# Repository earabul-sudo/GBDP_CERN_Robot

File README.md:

# GBDP_CERN_Robot

The report "20200524_PMReport_EA_04.pdf" can be read as the overview of the project.

The Complete CAD model can be found in;

https://a360.co/3e9NEjW

For any issues, please contact -> ea485@bath.ac.uk

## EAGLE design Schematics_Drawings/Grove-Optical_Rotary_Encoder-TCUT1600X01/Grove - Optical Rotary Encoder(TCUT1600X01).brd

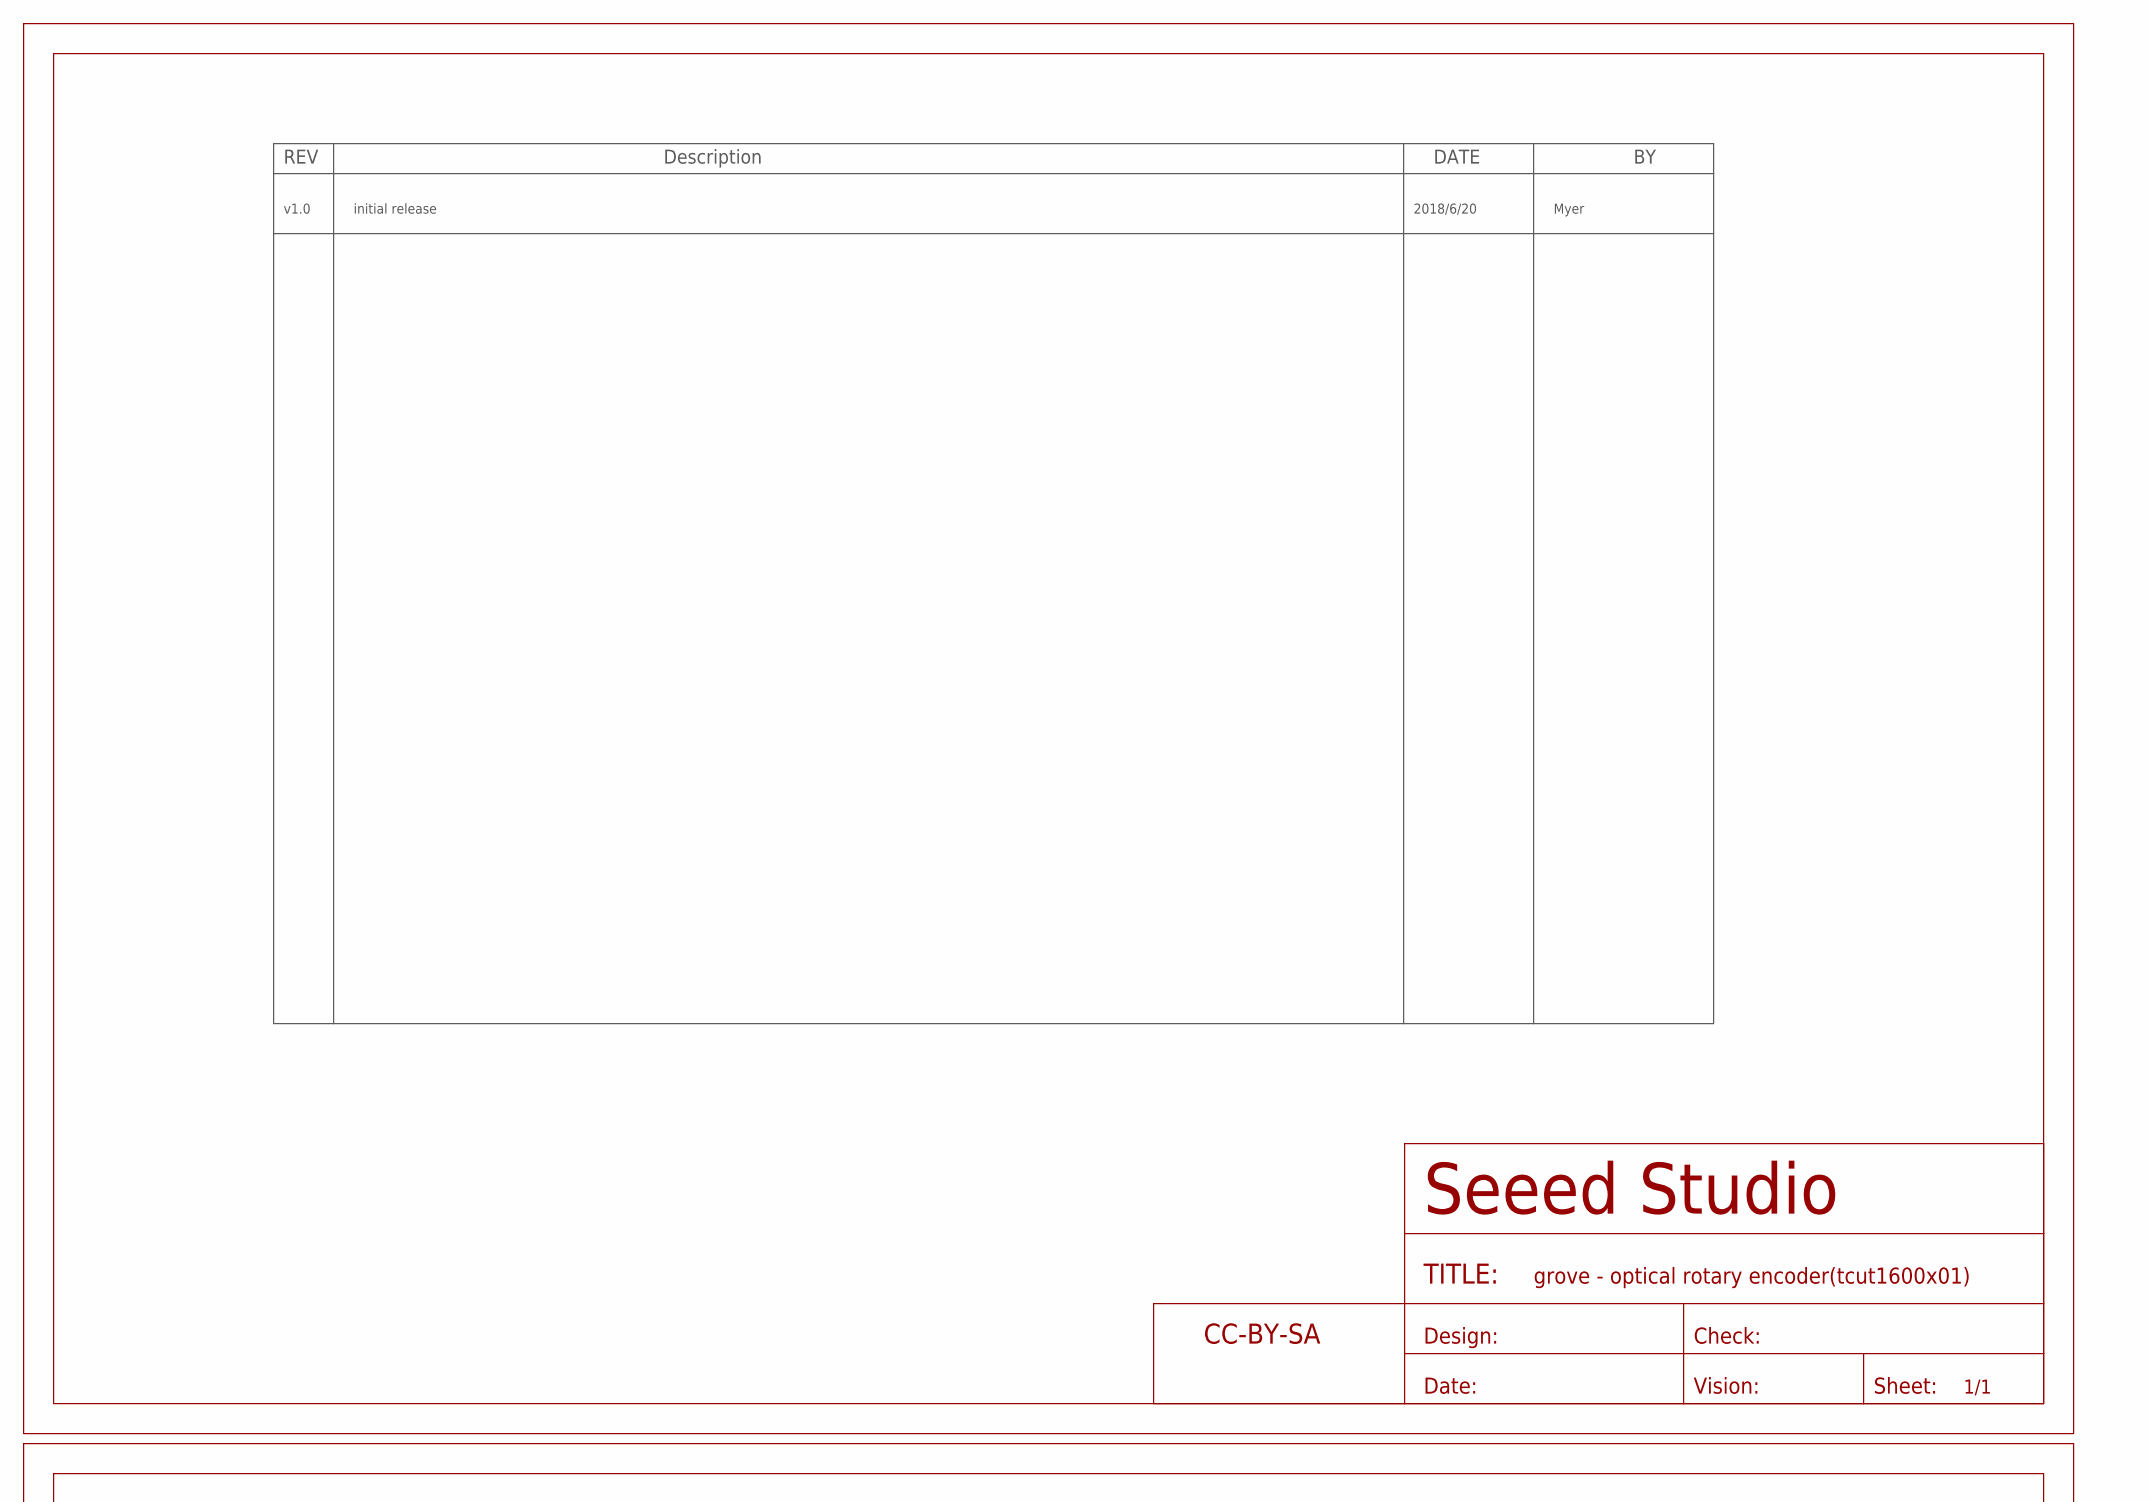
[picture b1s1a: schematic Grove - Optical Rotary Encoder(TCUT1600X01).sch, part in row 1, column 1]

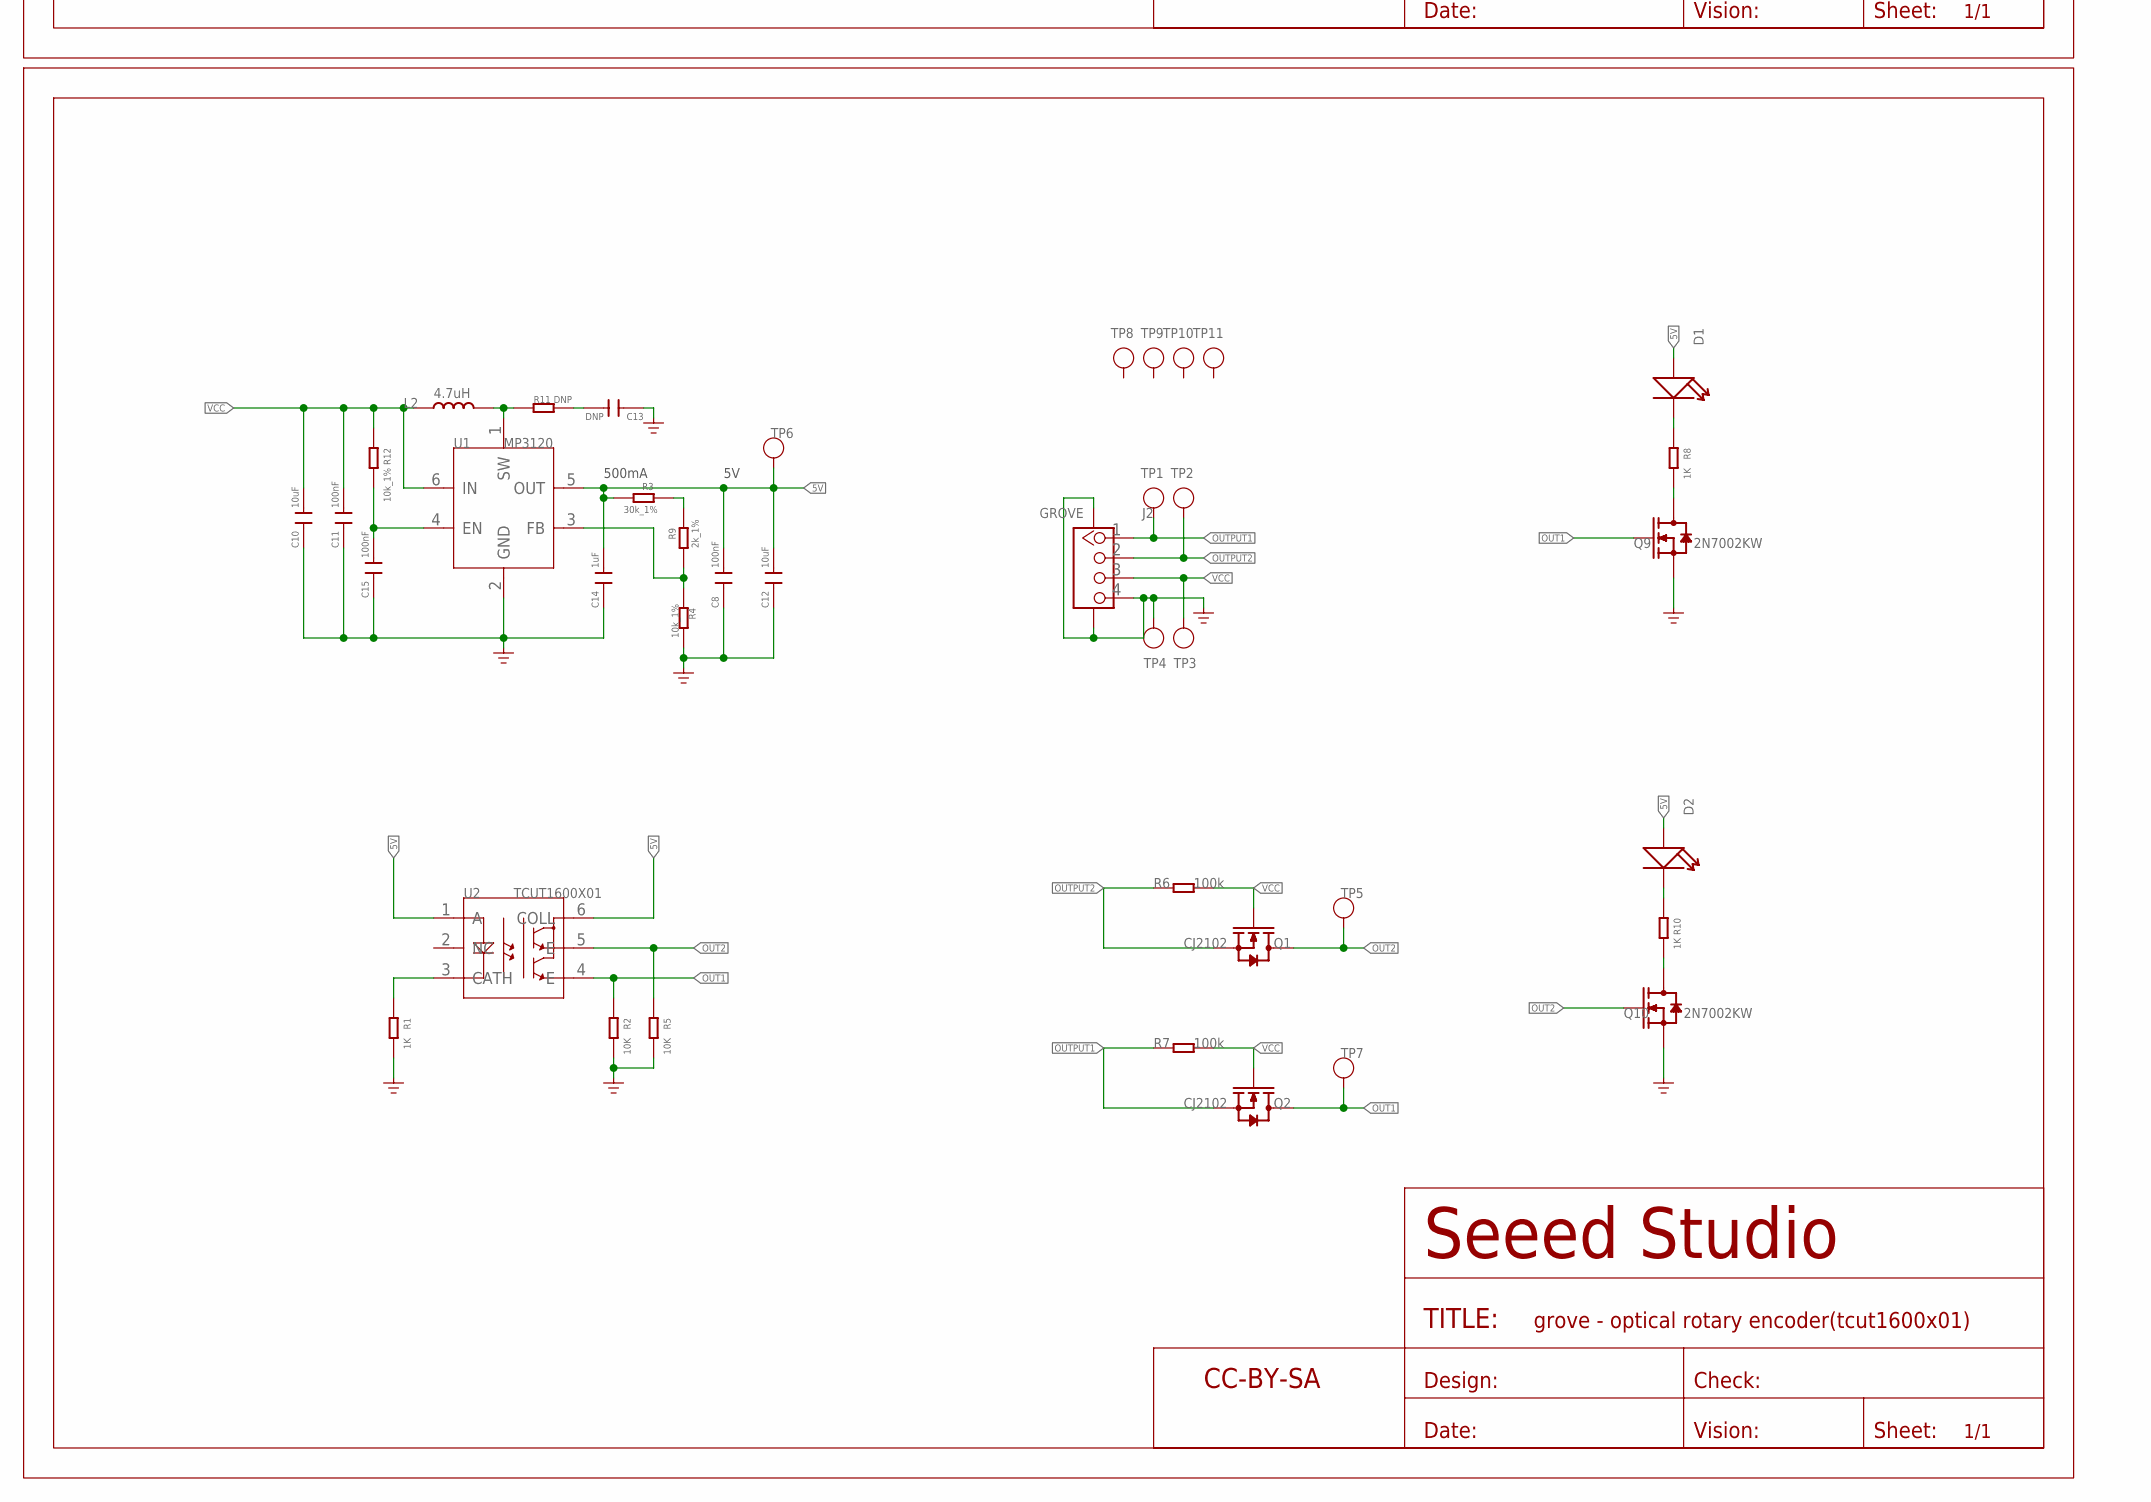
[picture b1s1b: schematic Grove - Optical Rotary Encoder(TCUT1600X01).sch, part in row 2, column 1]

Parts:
C8, C11, C15: 100nF; C0603
C10, C12: 10uF; C0603
C13: DNP; C0603
C14: 1uF; C0603
D1, D2: LED'0603'; LED-0603
FR1: SEEEDSTUDIO-OPEN-SCH-FRAME; SEEEDSTUDIO-PCB-FRAME
J2: GROVE; HW4-SMD-2.0
L2: 4.7uH; L2016
Q1, Q2: CJ2102; SOT-23@1
Q9, Q10: 2N7002KW; SOT-323
R1, R8, R10: 1K; R0603
R2, R5: 10K; R0603
R3: 30k_1%; R0603
R4, R12: 10k_1%; R0603
R6, R7: 100k; R0603
R9: 2k_1%; R0603
R11: DNP; R0603
TP1, TP2, TP3, TP4, TP5, TP6, TP7, TP8, TP9, TP10, TP11: TEST-POINT'4545'; TP-D45MIL
U1: MP3120; SOT-23-6
U2: TCUT1600X01; SNR6-1.4-5.5X4X5.7MM
U$4: SEEEDSTUDIO-OPEN-SCH-FRAME; SEEEDSTUDIO-PCB-FRAME

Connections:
5V: C8.2, C12.2, C14.2, D1.+, D2.+, R3.2, TP6.T, U1.5 (OUT), U2.1 (A), U2.6 (COLL)
GND: C8.1, C10.1, C11.1, C12.1, C13.1, C14.1, C15.1, J2.4, J2.SS1, J2.SS2, Q9.2 (S), Q10.2 (S), R1.2, R2.2, R4.1, R5.2, TP4.T, U1.2 (GND)
unnamed: R1.1, U2.3 (CATH)
unnamed: R4.2, R9.2, U1.3 (FB)
unnamed: R3.1, R9.1
unnamed: L2.2, R11.1, U1.1 (SW)
unnamed: C13.2, R11.2
unnamed: C15.2, R12.2, U1.4 (EN)
unnamed: Q9.3 (D), R8.2
unnamed: D1.-, R8.1
unnamed: Q10.3 (D), R10.2
unnamed: D2.-, R10.1
OUT1: Q2.3 (D), Q9.1 (G), R2.1, TP7.T, U2.4 (E)
OUT2: Q1.3 (D), Q10.1 (G), R5.1, TP5.T, U2.5 (E)
OUTPUT1: J2.1, Q2.2 (S), R7.1, TP1.T
OUTPUT2: J2.2, Q1.2 (S), R6.1, TP2.T
VCC: C10.2, C11.2, J2.3, L2.1, Q1.1 (G), Q2.1 (G), R6.2, R7.2, R12.1, TP3.T, U1.6 (IN)

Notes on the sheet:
500mA
initial release
v1.0
2018/6/20
Myer

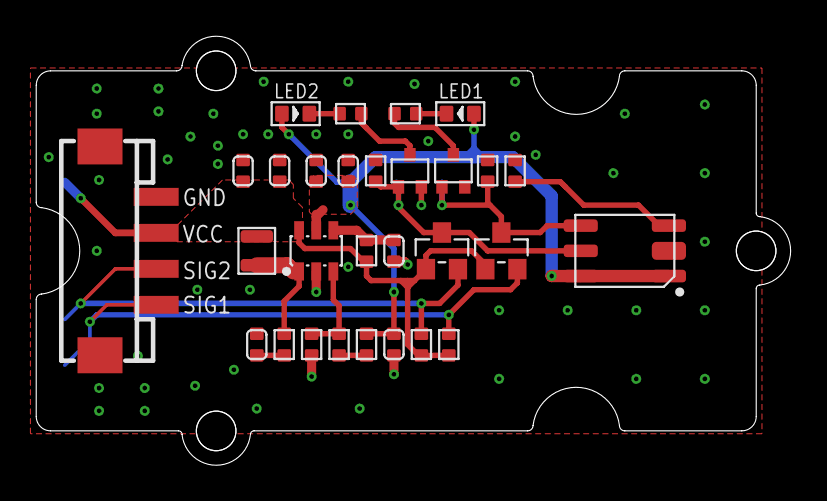
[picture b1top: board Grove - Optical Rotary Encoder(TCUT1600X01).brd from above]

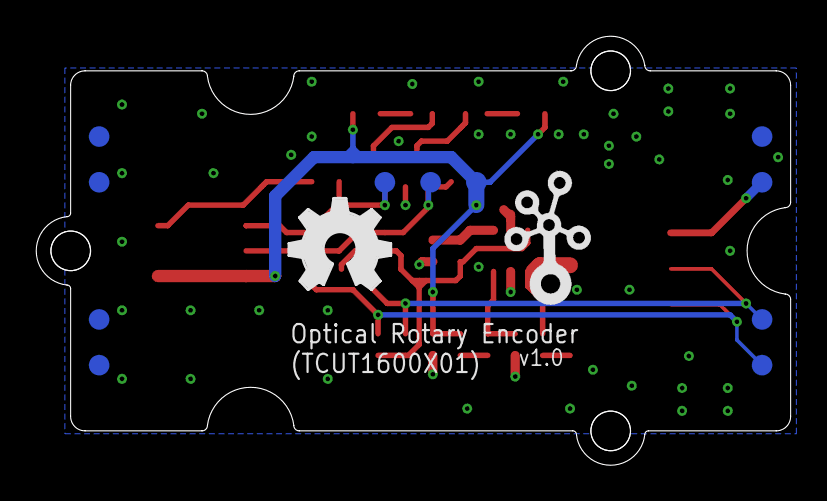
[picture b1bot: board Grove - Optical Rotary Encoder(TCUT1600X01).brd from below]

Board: 2 copper layers, 41.9 x 23.8 mm, 45 parts (13 on the bottom side), 17 nets.

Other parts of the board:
U$10: GROVE-1*2-TEST-PLATFORM-TOP
U$11: TWIGLOGO
U$13: OSHW_FILLX200_NOTEXT

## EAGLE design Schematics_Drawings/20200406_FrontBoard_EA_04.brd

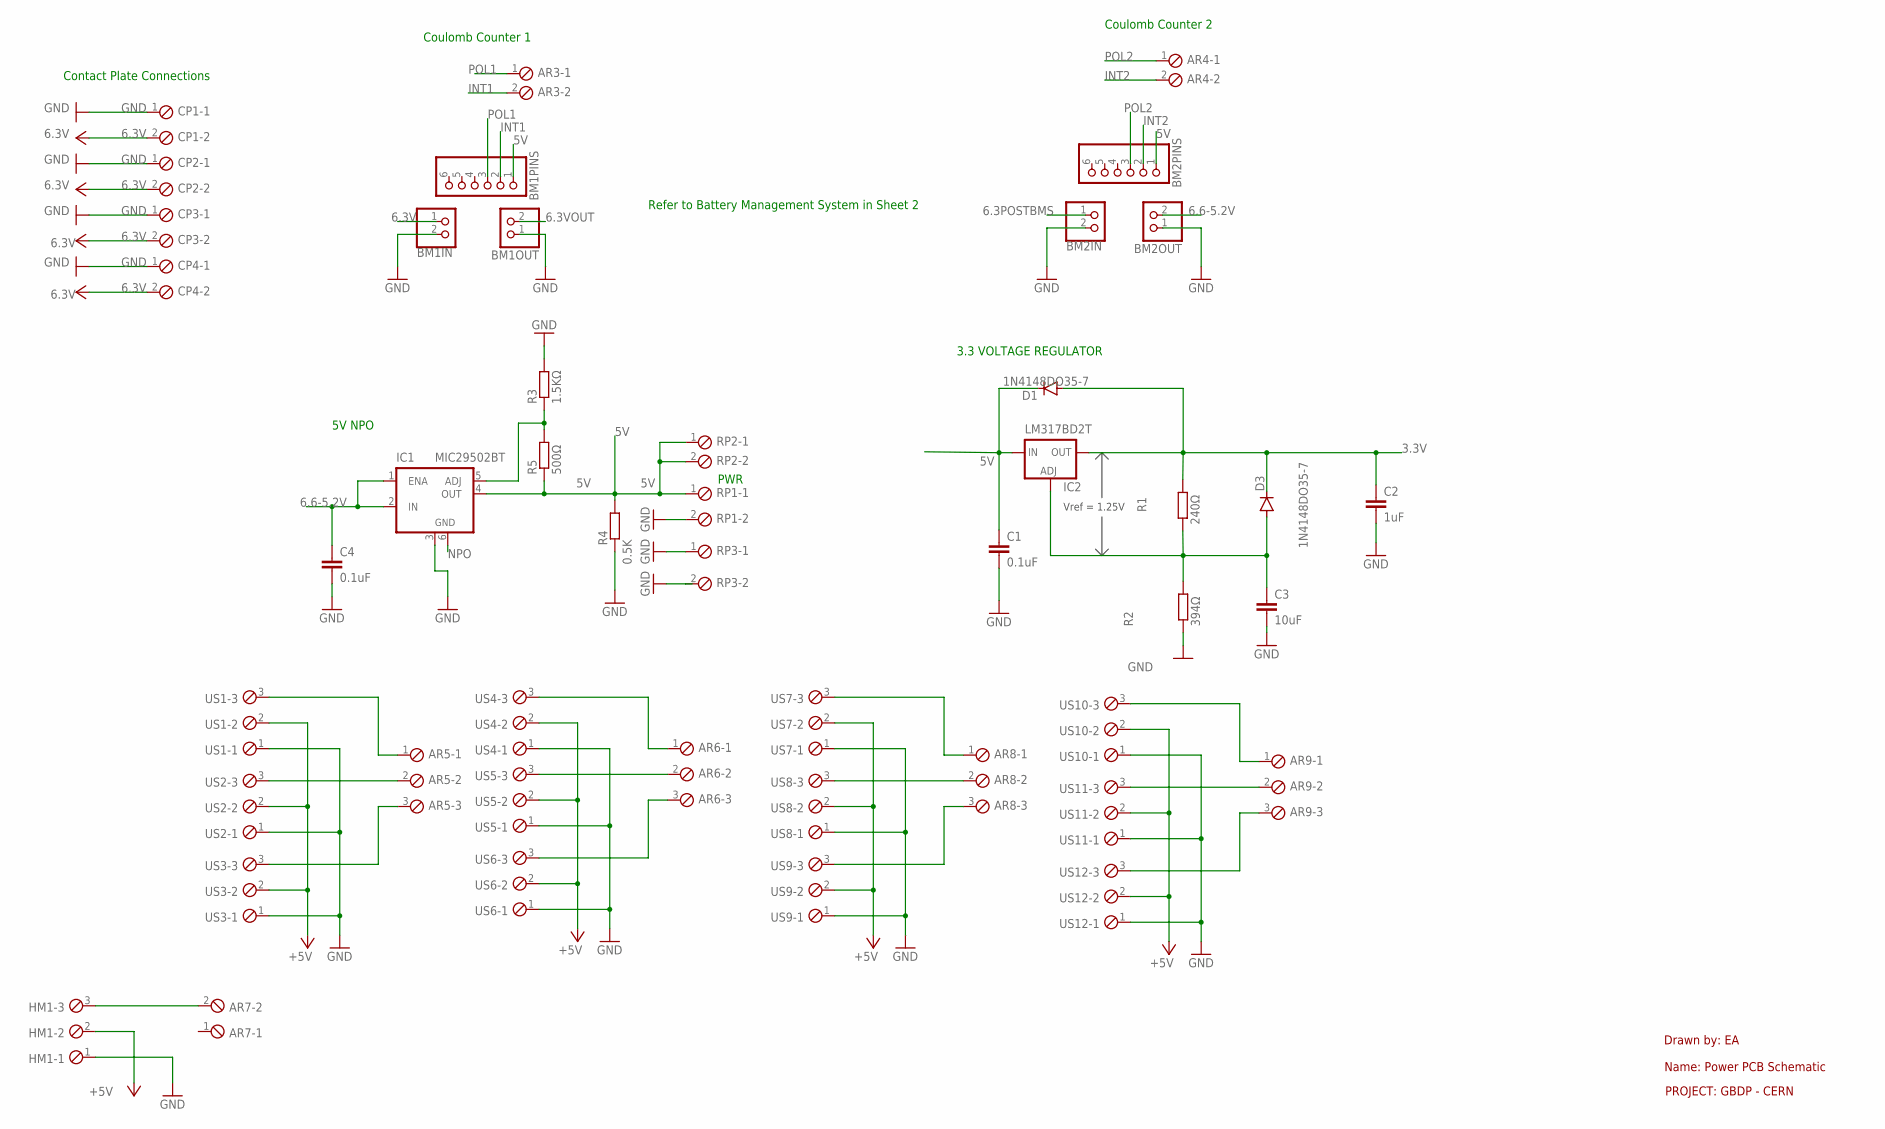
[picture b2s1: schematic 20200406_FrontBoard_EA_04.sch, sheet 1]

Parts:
AR3, AR4, AR7: MPT2; 2POL254
AR5, AR6, AR8, AR9: MPT3; 3POL254
BM1IN, BM1OUT, BM2IN, BM2OUT: PINHD-1X2; 1X02
BM1PINS, BM2PINS: PINHD-1X6; 1X06
C1, C4: 0.1uF; C025-025X050
C2: 1uF; C025-025X050
C3: 10uF; C025-025X050
CP1, CP2, CP3, CP4: MPT2; 2POL254
D1, D3: 1N4148DO35-7; DO35-7
HM1: MPT3; 3POL254
IC1: MIC29502BT; TO263-5
IC2: LM317BD2T; D2PACK
R1: 240Ω; 0204/7
R2: 394Ω; 0204/7
R3: 1.5KΩ; 0204/7
R4: 0.5K; 0204/7
R5: 500Ω; 0204/7
RP1, RP2, RP3: MPT2; 2POL254
US1, US2, US3, US4, US5, US6, US7, US8, US9, US10, US11, US12: MPT3; 3POL254

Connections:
3.3V: C2.1, D1.A, D3.C, IC2.2 (OUT), R1.2
5V: BM1PINS.1, BM2PINS.1, C1.1, D1.C, IC1.4 (OUT), IC2.3 (IN), R4.2, R5.1, RP1.1, RP2.1, RP2.2
6.3POSTBMS: BM2IN.1; also elsewhere on the board
6.3V: BM1IN.1, CP1.2, CP2.2, CP3.2, CP4.2
6.3VOUT: BM1OUT.2; also elsewhere on the board
6.6-5.2V: BM2OUT.2, C4.1, IC1.1 (ENA), IC1.2 (IN)
+5V: HM1.2, US1.2, US2.2, US3.2, US4.2, US5.2, US6.2, US7.2, US8.2, US9.2, US10.2, US11.2, US12.2
GND: BM1IN.2, BM1OUT.1, BM2IN.2, BM2OUT.1, C1.2, C2.2, C3.2, C4.2, CP1.1, CP2.1, CP3.1, CP4.1, HM1.1, IC1.3 (GND), R2.1, R3.2, R4.1, RP1.2, RP3.1, RP3.2, US1.1, US2.1, US3.1, US4.1, US5.1, US6.1, US7.1, US8.1, US9.1, US10.1, US11.1, US12.1; also elsewhere on the board
INT1: AR3.2, BM1PINS.2
INT2: AR4.2, BM2PINS.2
unnamed: C3.1, D3.A, IC2.1 (ADJ), R1.1, R2.2
unnamed: AR8.3, US9.3
unnamed: IC1.5 (ADJ), R3.1, R5.2
unnamed: AR5.3, US3.3
unnamed: AR5.2, US2.3
unnamed: AR5.1, US1.3
unnamed: AR6.3, US6.3
unnamed: AR6.2, US5.3
unnamed: AR6.1, US4.3
unnamed: AR7.2, HM1.3
unnamed: AR8.2, US8.3
unnamed: AR8.1, US7.3
unnamed: AR9.3, US12.3
unnamed: AR9.2, US11.3
unnamed: AR9.1, US10.3
NPO: IC1.6 (GND)
POL1: AR3.1, BM1PINS.3
POL2: AR4.1, BM2PINS.3

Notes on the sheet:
Vref = 1.25V
PWR
Contact Plate Connections
Coulomb Counter 1
Coulomb Counter 2
Refer to Battery Management System in Sheet 2
5V NPO
3.3 VOLTAGE REGULATOR
Drawn by: EA
Name: Power PCB Schematic
PROJECT: GBDP - CERN

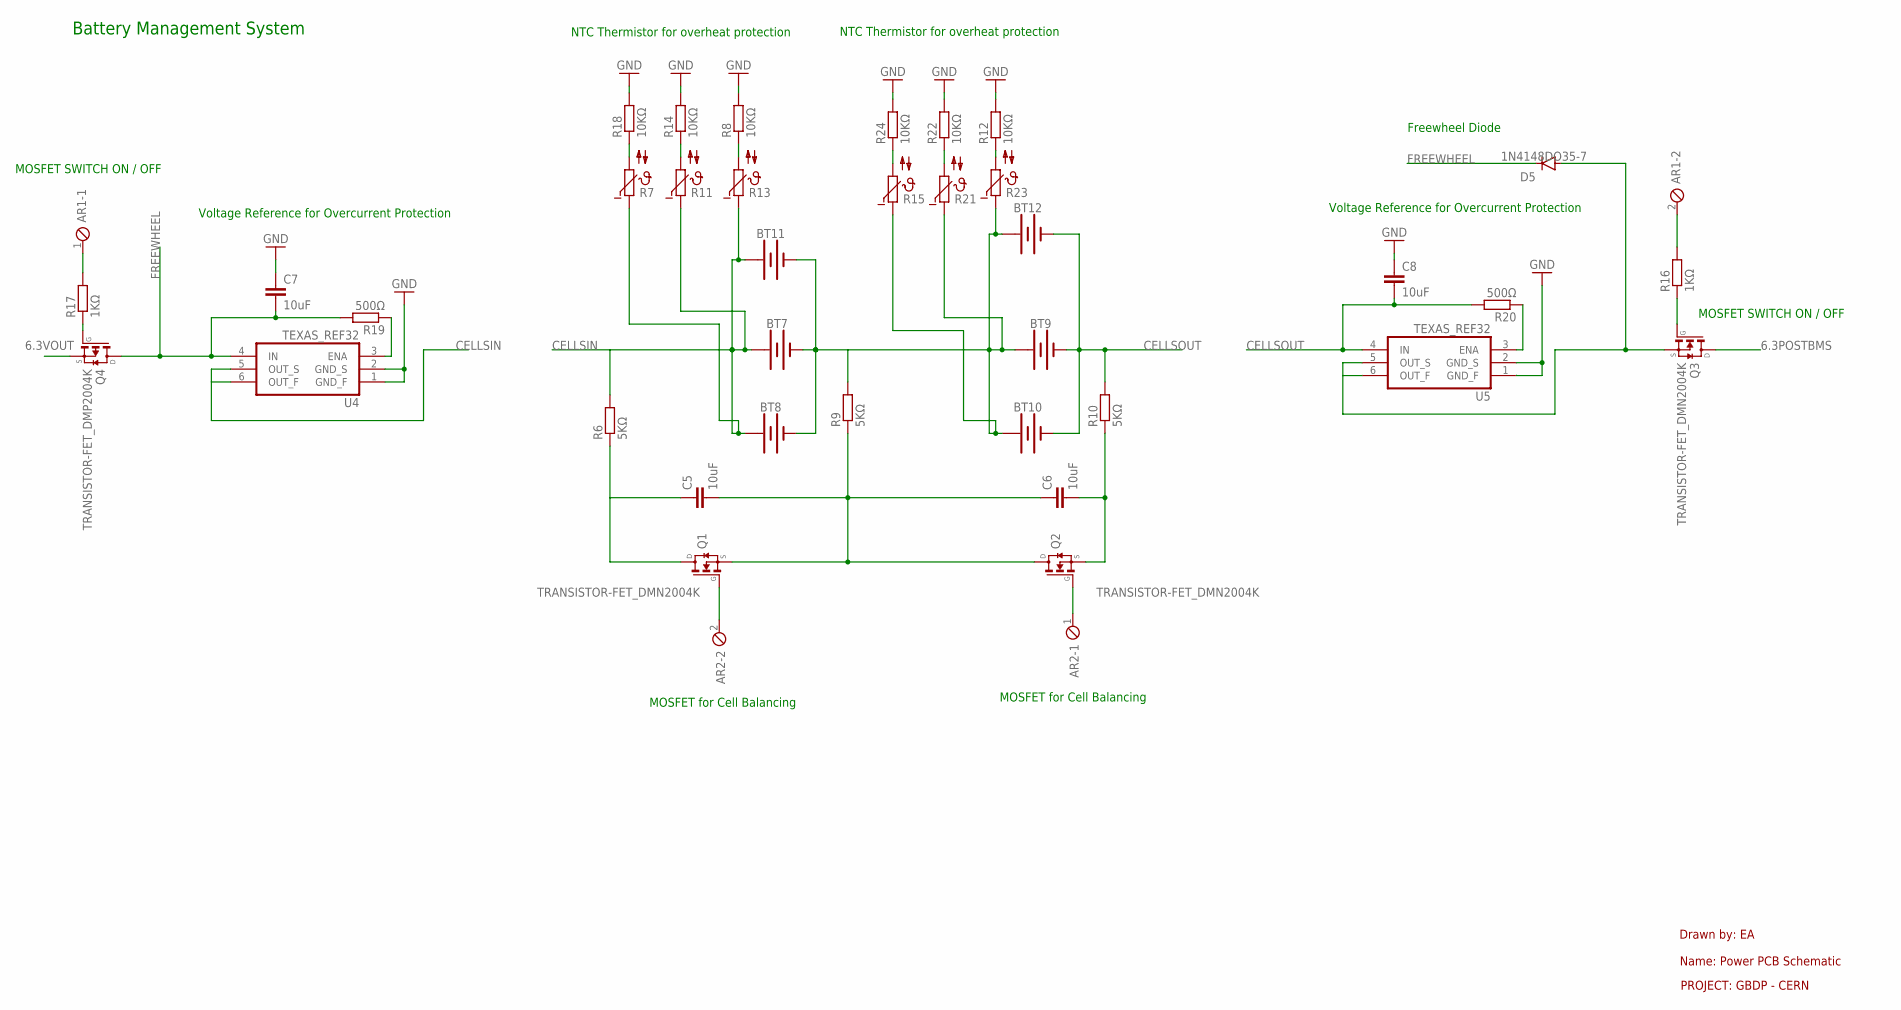
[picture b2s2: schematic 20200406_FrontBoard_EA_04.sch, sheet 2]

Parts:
AR1, AR2: MPT2; 2POL254
BT7, BT8, BT9, BT10, BT11, BT12: BATTERY-18650; BATTERY_18650-HOLDER
C5, C6, C7, C8: 10uF; C025-025X050
D5: 1N4148DO35-7; DO35-7
Q1, Q2, Q3: TRANSISTOR-FET_DMN2004K; TRANSISTOR-FET_SOT23
Q4: TRANSISTOR-FET_DMP2004K; TRANSISTOR-FET_SOT23
R6, R9, R10: 5KΩ; 0204/7
R7, R11, R13, R15, R21, R23: NTC640; P640
R8, R12, R14, R18, R22, R24: 10KΩ; 0204/7
R16, R17: 1KΩ; 0204/7
R19, R20: 500Ω; 0204/7
U4, U5: TEXAS_REF32; TEXAS_SOT23-6

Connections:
6.3POSTBMS: Q3.3 (D); also elsewhere on the board
6.3VOUT: Q4.2 (S); also elsewhere on the board
CELLSIN: BT7.PWR@1 (+), BT8.PWR@1 (+), BT11.PWR@1 (+), R6.2, R7.1, R11.1, R13.1, U4.5 (OUT_S), U4.6 (OUT_F)
CELLSOUT: BT9.GND@1 (-), BT10.GND@1 (-), BT12.GND@1 (-), C8.2, R10.2, R20.2, U5.4 (IN)
FREEWHEEL: C7.2, D5.C, Q4.3 (D), R19.2, U4.4 (IN)
GND: C7.1, C8.1, R8.2, R12.2, R14.2, R18.2, R22.2, R24.2, U4.1 (GND_F), U4.2 (GND_S), U5.1 (GND_F), U5.2 (GND_S); also elsewhere on the board
unnamed: C5.2, C6.1, Q1.2 (S), Q2.3 (D), R9.1
unnamed: C6.2, Q2.2 (S), R10.1
unnamed: AR2.2, Q1.1 (G)
unnamed: AR2.1, Q2.1 (G)
unnamed: AR1.2, R16.2
unnamed: D5.A, Q3.2 (S), U5.5 (OUT_S), U5.6 (OUT_F)
unnamed: Q3.1 (G), R16.1
unnamed: Q4.1 (G), R17.1
unnamed: AR1.1, R17.2
unnamed: R8.1, R13.2
unnamed: R21.2, R22.1
unnamed: C5.1, Q1.3 (D), R6.1
unnamed: R19.1, U4.3 (ENA)
unnamed: R12.1, R23.2
unnamed: R20.1, U5.3 (ENA)
unnamed: R11.2, R14.1
unnamed: R7.2, R18.1
unnamed: BT7.GND@1 (-), BT8.GND@1 (-), BT9.PWR@1 (+), BT10.PWR@1 (+), BT11.GND@1 (-), BT12.PWR@1 (+), R9.2, R15.1, R21.1, R23.1
unnamed: R15.2, R24.1

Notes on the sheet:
Drawn by: EA
Name: Power PCB Schematic
PROJECT: GBDP - CERN
MOSFET SWITCH ON / OFF
Freewheel Diode
NTC Thermistor for overheat protection
MOSFET for Cell Balancing
Voltage Reference for Overcurrent Protection
Battery Management System

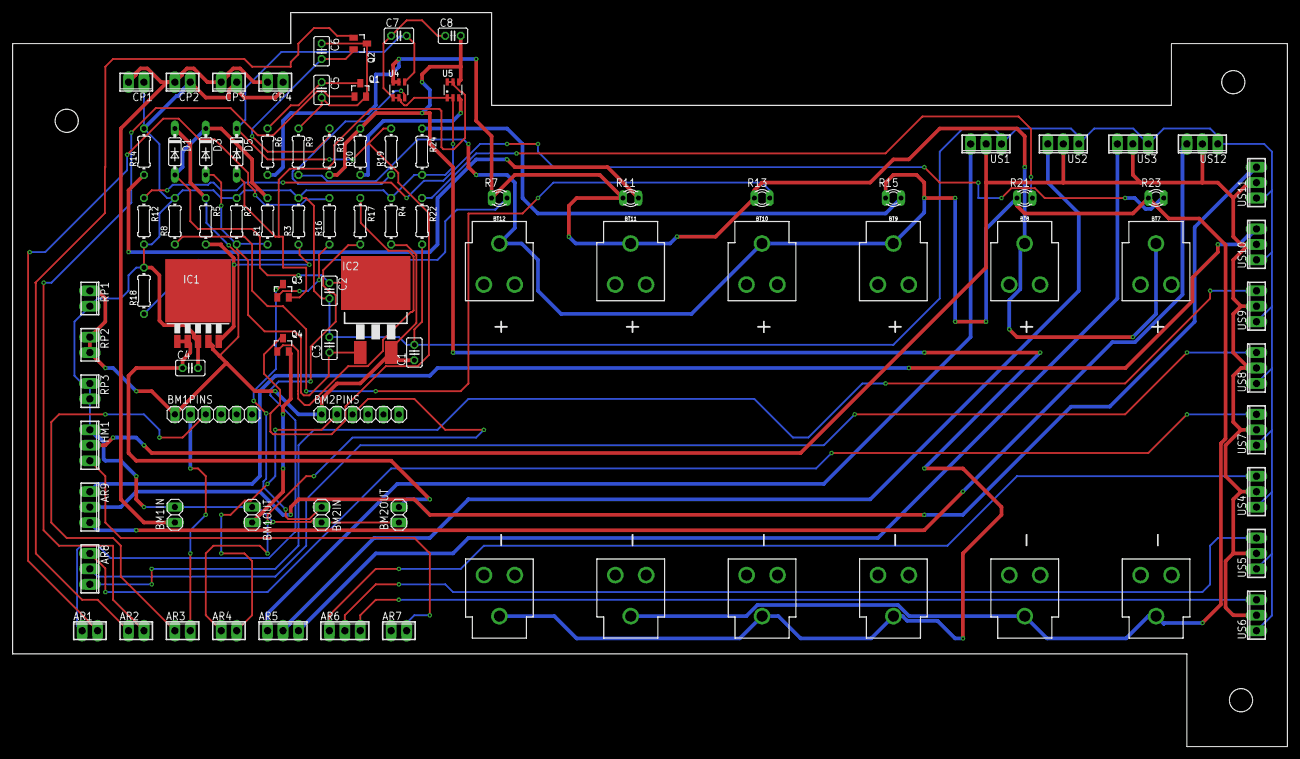
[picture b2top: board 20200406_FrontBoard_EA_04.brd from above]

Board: 2 copper layers, 209.6 x 120.7 mm, 84 parts (0 on the bottom side), 49 nets.

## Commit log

2020-06-28 new file: 20200524_PMReport_EA_04.pdf
2020-06-28 new file: Renders/20200406_FrontBoard_EA_04_2020-May-25_08-08-47AM-000_CustomizedView26765888059_png.png new file: Renders/20200413_RaspberryPiStack_EA_00_2020-May-25_08-18-17AM-000_CustomizedView224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
2020-06-28 modified: README.md
2020-06-28 new file: Schematics_Drawings/20200406_FrontBoard_EA_04.brd new file: Schematics_Drawings/20200406_FrontBoard_EA_04.sch new file: Schematics_Drawings/20200413_Systems_EA_00.sch new file: Schematics_D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
2020-06-28 new file: CMS cavern testing v2.ttt

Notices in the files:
parts and their libraries:
SparkFun-Batteries_edited: Licensing: Creative Commons ShareAlike 4.0 International - https://creativecommons.org/licenses/by-sa/4.0
moudle-new: This work is licensed under the Creative Commons Attribution 4.0 International License.
To view a copy of this license,visit: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
moudle-new: CC-BY-SA
